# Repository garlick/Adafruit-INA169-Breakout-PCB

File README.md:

# Load switch and power measurement breakout

Breakout board containing TI TPS22958 DC load switch
and INA169 analog DC power measurement.  The target
load is the 5V supply of a Raspberry Pi version 3.

Uses 24-pin 600mil DIP form factor.

## forked from Adafruit-INA169-Breakout-PCB

PCB files for Adafruit INA169 Analog DC power measurement Breakout

Format is EagleCAD schematic and board layout

For more details, check out the product page at

  * https://www.adafruit.com/product/1164

Adafruit invests time and resources providing this open source design, 
please support Adafruit and open-source hardware by purchasing 
products from Adafruit!

Designed by Adafruit Industries.  
Creative Commons Attribution, Share-Alike license, check license.txt for more information
All text above must be included in any redistribution

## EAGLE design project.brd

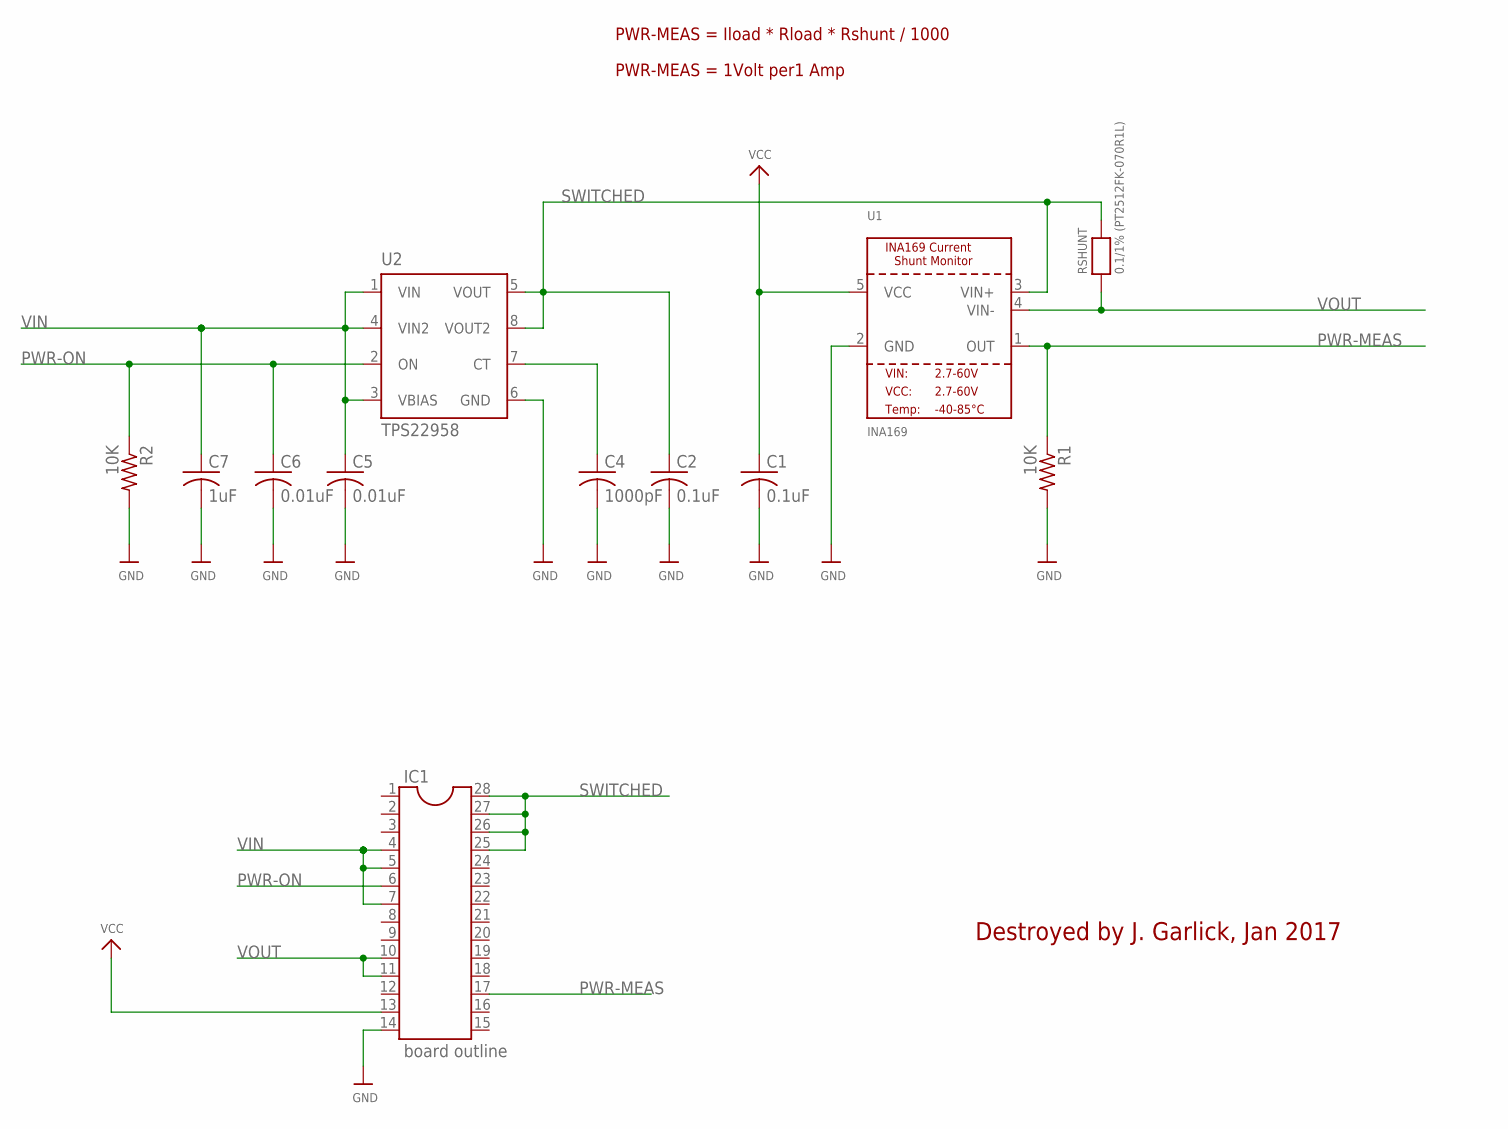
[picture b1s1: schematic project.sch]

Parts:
C1, C2: 0.1uF; C1206K
C4: 1000pF; C1206K
C5, C6: 0.01uF; C1206K
C7: 1uF; C1206K
IC1: board outline; DIL28-6
R1, R2: 10K; M1206
RSHUNT: 0.1/1% (PT2512FK-070R1L); 2512
U1: INA169; SOT23-5
U2: TPS22958; S-PDSO-G08

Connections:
CT: C4.1, U2.7 (CT)
GND: C1.2, C2.2, C4.2, C5.2, C6.2, C7.2, IC1.14, R1.2, R2.2, U1.2 (GND), U2.6 (GND)
PWR-MEAS: IC1.17, R1.1, U1.1 (OUT)
PWR-ON: C6.1, IC1.6, R2.1, U2.2 (ON)
SWITCHED: C2.1, IC1.25, IC1.26, IC1.27, IC1.28, RSHUNT.2, U1.3 (VIN+), U2.5 (VOUT), U2.8 (VOUT2)
VCC: C1.1, IC1.13, U1.5 (VCC)
VIN: C5.1, C7.1, IC1.4, IC1.5, IC1.7, U2.1 (VIN), U2.3 (VBIAS), U2.4 (VIN2)
VOUT: IC1.10, IC1.11, RSHUNT.1, U1.4 (VIN-)

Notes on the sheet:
PWR-MEAS = Iload * Rload * Rshunt / 1000
PWR-MEAS = 1Volt per1 Amp
Destroyed by J. Garlick, Jan 2017

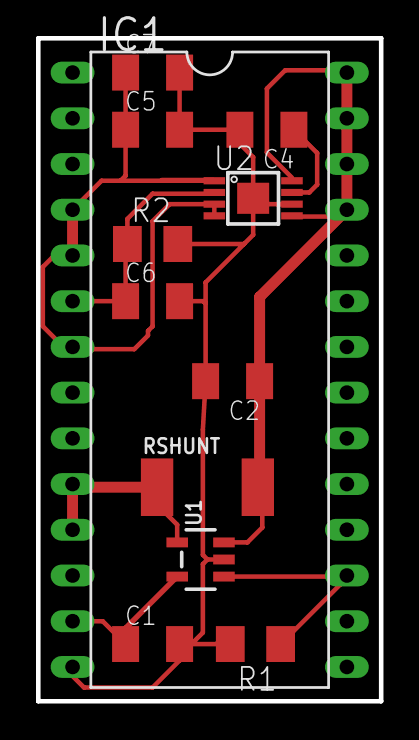
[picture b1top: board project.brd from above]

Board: 2 copper layers, 19.1 x 36.8 mm, 12 parts (0 on the bottom side), 8 nets.

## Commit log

2017-01-15 README: update fork description
2017-01-16 add load switch and rework for 24p DIL 600mil outline
2017-01-16 resize pdf
2017-01-22 add makefile with clean target
2017-01-22 rename project files
2017-01-22 Makefile: generate gerbers
2017-01-22 project.brd: add milling layer for board outline
2017-01-22 project.sch: replace frame with generic one
2017-01-22 README.md: mention form factor
